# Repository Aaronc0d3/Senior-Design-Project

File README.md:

# Senior-Design-Project
Contributions for the TARS system
This Repo is a collection of all the contributions that I have done for my Senior Design Class at Kennesaw State University. 
I was tasked with creating the Bin Detection system to notify the user of how full the bins were within the container.
I would also like to thank Joshua Olaniran and Kiano Watson for being excellent partners during this class and helping me along the way.

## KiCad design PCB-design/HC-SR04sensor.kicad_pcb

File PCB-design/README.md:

This is files containg my PCB design, which holds an HC-SR04 Ultrasonic Sensor, a red and green led, male GPIO ports, and some resistors

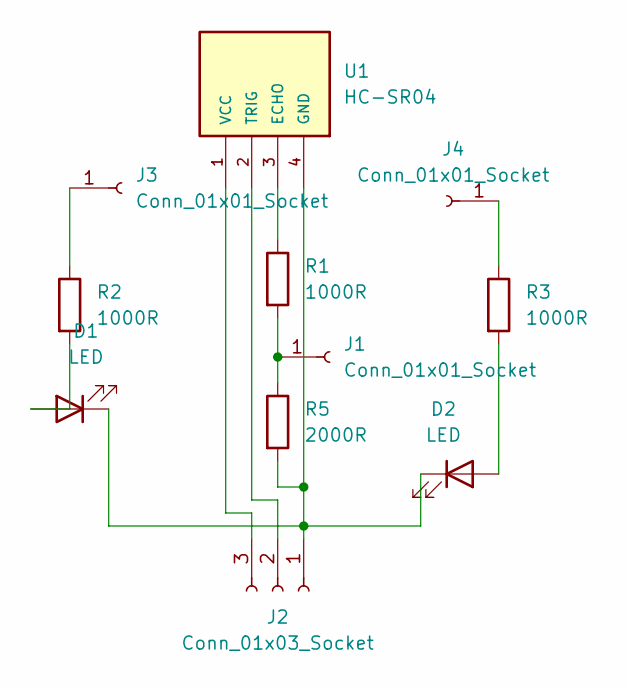
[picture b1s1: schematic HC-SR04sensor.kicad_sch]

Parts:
D1, D2: LED; LED_D3.0mm_Horizontal_O6.35mm_Z10.0mm
J1, J3, J4: Conn_01x01_Socket; PinSocket_1x01_P2.54mm_Vertical
J2: Conn_01x03_Socket; PinSocket_1x03_P2.54mm_Vertical
R1, R2, R3: 1000R; Resistor_holes
R5: 2000R; Resistor_holes
U1: HC-SR04; XCVR_HC-SR04

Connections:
unnamed: D1.2 (A), R2.2
unnamed: D1.1 (K), D2.1 (K), J2.1, R5.2, U1.4 (GND)
unnamed: D2.2 (A), R3.2
unnamed: J1.1, R1.2, R5.1
unnamed: J2.2, U1.2 (TRIG)
unnamed: J2.3, U1.1 (VCC)
unnamed: J3.1, R2.1
unnamed: J4.1, R3.1
unnamed: R1.1, U1.3 (ECHO)

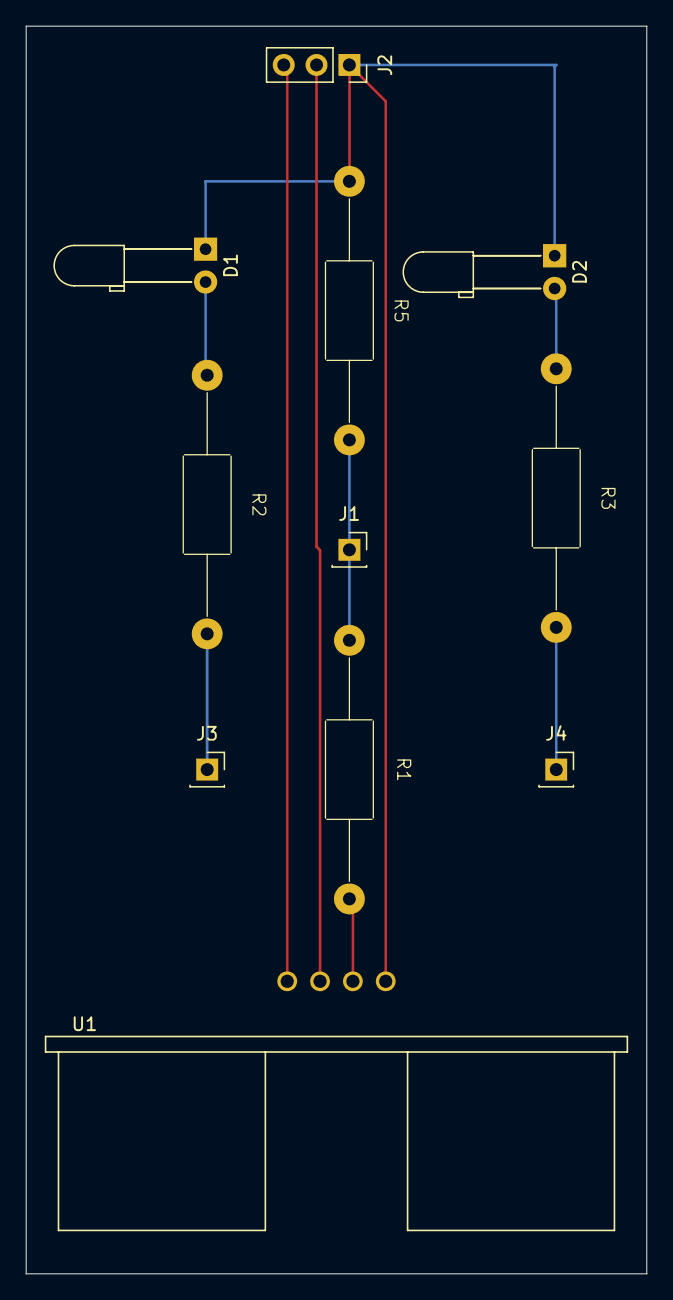
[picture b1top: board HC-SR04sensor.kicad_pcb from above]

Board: 2 copper layers, 48.0 x 96.5 mm, 11 parts (0 on the bottom side), 9 nets.

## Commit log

2024-12-10 Rename README.md to 3D-PRINTS.md
2024-12-10 Rename 3D-PRINTS.md to 3DPRINTS.md
2024-12-11 Rename 3DPRINT.md to README.md
